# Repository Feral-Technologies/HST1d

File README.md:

HST1d FERAL TECHNOLOGIES AKA The Music Technology Frisbee (as christened by Electronic Instruments students 2018) is a six-voice portable and battery powered synthesiser based around a 40106 (Hex Schmitt-Trigger). 

Three voices are operated via resistive-touch on the MuTec lettering;

Three voices can be either light-sensitive (photocells) or controlled via potentiometers, the control method is individually switchable for each of these three voices;

The range of the three light/potentiometer-controlled voices is switchable high/low;

Lighting/pitch control is laid out horizontally across the board while from an output perspective the instrument is divided in half down the middle, with two separate volume controls: one for the three touch sensitive voices and the other for the three light/potentiometer voices;

The three individual voices that make up each of the two halves of the instrument can either be mixed via diodes or resistors (switchable), which offers further timbral manipulation;

Output is via mono ¼ inch jack socket on the rear (along with the off/on switch) and/or the onboard amplifier/speaker combination using an LM386 (switchable, and both can be used simultaneously, though there’s no buffering so this can impact tone–I should add an op-amp in future);

Power is via 9-volt battery which clips into a socket on the rear, this also makes the whole thing stable and sit nicely/angled towards the performer when used as as a desktop instrument;

LEDs articulate interactions with the touch-sensitive side of the circuit;

Two of the LEDs on the touch circuit are deliberately placed near the photocells that control two of the other voices, if desired these can be bent towards each other (and even taped together/mounted in a straw) for vactrol fun and interaction.

In case anyone actually try to build this it’s worth noting this I had to make my own footprints for the switches as I had bought a large quantity very cheaply and the spacing was not quite what I anticipated, some standard switches do not fit – always best to print out and check components by pushing through the paper! (I learned this the hard way…..)

See HST1d_Feral_Technologies_2018.pdf for full build documentation with step-by-step build instructions, parts list, and a photograph of each stage (this was made for my 2018 teaching of 2710QCM Electronic Instruments @ QCGU).

More information 
http://www.johnrobertferguson.com/hst1d-feral-technologies/

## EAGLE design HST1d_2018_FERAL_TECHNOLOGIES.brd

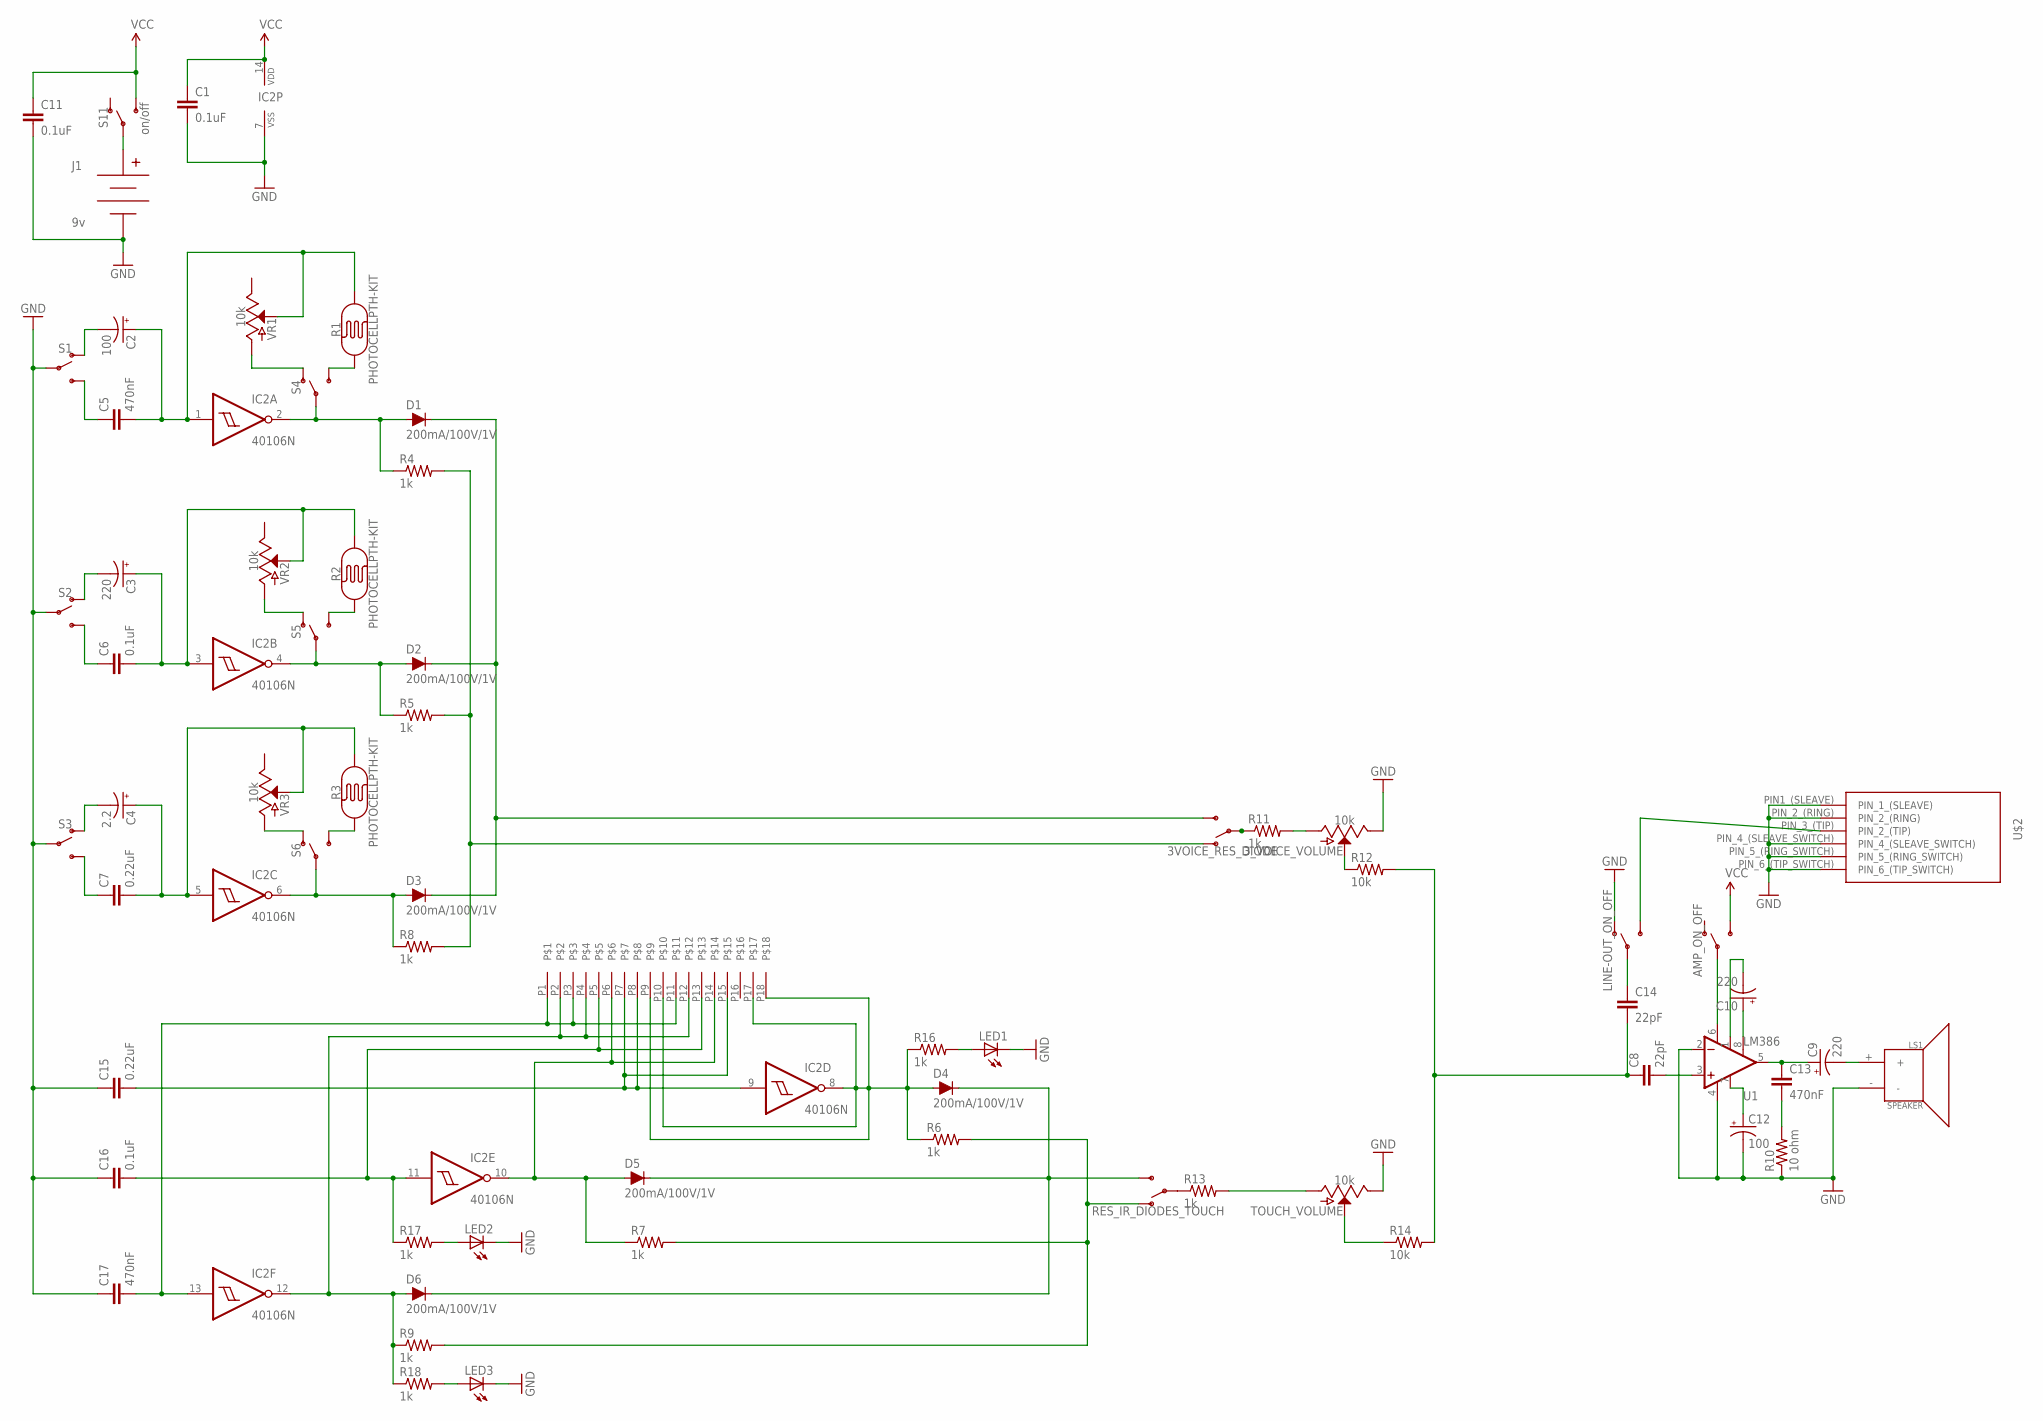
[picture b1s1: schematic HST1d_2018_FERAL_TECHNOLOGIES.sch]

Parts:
3VOICE_RES_DIODE: SWITCH-SPDT-PTH-11.6X4.0MM; SWITCH_SPDT_PTH_11.6X4.0MM
3_VOICE_VOLUME: 10k; POT-PTH-ALPS
AMP_ON_OFF: SWITCH-SPDT-PTH-11.6X4.0MM; SWITCH_SPDT_PTH_11.6X4.0MM
C1, C6, C11, C16: 0.1uF; CAP-PTH-SMALL-KIT
C2, C12: 100; CPOL-RADIAL-100UF-25V
C3, C9, C10: 220; CPOL-RADIAL-100UF-25V
C4: 2.2; CPOL-RADIAL-100UF-25V
C5, C17: 470nF; CAP-PTH-SMALL-KIT
C7, C15: 0.22uF; CAP-PTH-SMALL-KIT
C8, C14: 22pF; CAP-PTH-2.54
C13: 470nF; CAP-PTH-SMALLEZ
D1, D2, D3, D4, D5, D6: 200mA/100V/1V; DIODE-1N4148
IC2: 40106N; DIL14
J1: 9v; BC9VPC
LED1, LED2, LED3: LED5MM
LINE-OUT_ON_OFF: SWITCH-SPDT-PTH-11.6X4.0MM; SWITCH_SPDT_PTH_11.6X4.0MM
LS1: SPEAKER; PCB_MOUNT_SPEAKER
R1, R2, R3: PHOTOCELLPTH-KIT; PHOTOCELL-KIT
R4, R5, R6, R7, R8, R9, R11, R13, R16, R17, R18: 1k; AXIAL-0.4
R10: 10 ohm; AXIAL-0.4
R12, R14: 10k; AXIAL-0.4
RES_IR_DIODES_TOUCH: SWITCH-SPDT-PTH-11.6X4.0MM; SWITCH_SPDT_PTH_11.6X4.0MM
S1, S2, S3, S4, S5, S6: SWITCH-SPDT-PTH-11.6X4.0MM; SWITCH_SPDT_PTH_11.6X4.0MM
S11: on/off; SWITCH_SPDT_PTH_11.6X4.0MM
TOUCH_VOLUME: 10k; POT-PTH-ALPS
U1: LM386; DIP08
U$1: MT_TOUCH_POINT; TOUCH_POINT
U$2: 0.25_INCH_TRS_SWITCHED_AUDIO_SOCKET; 0.25INCH_AUDIO_SOCKET
VR1, VR2, VR3: 10k; POT-PTH-ALPS

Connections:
GND: 3_VOICE_VOLUME.P$1 (E), C1.2, C11.2, C12.2 (-), C15.1, C16.1, C17.1, IC2.7 (VSS), J1.V-, LED1.K (C), LED2.K (C), LED3.K (C), LINE-OUT_ON_OFF.1 (O), LS1.-, R10.P$1 (1), S1.2, S2.2, S3.2, TOUCH_VOLUME.P$1 (E), U1.2 (-IN), U1.4 (V-), U$2.PIN1_(SLEAVE) (PIN_1_(SLEAVE)), U$2.PIN_2_(RING), U$2.PIN_4_(SLEAVE_SWITC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, U$2.PIN_5_(RING_SWITCH), U$2.PIN_6_(TIP_SWITCH)
unnamed: C2.2 (-), S1.1 (O)
unnamed: C3.2 (-), S2.1 (O)
unnamed: C4.2 (-), S3.1 (O)
unnamed: C5.1, S1.3 (S)
unnamed: C2.1 (+), C5.2, IC2.1 (I), R1.2, VR1.P$2 (S)
unnamed: C6.1, S2.3 (S)
unnamed: D2.A, IC2.4 (O), R5.P$1 (1), S5.2
unnamed: C7.1, S3.3 (S)
unnamed: R1.1, S4.3 (S)
unnamed: D3.A, IC2.6 (O), R8.P$1 (1), S6.2
unnamed: S4.1 (O), VR1.P$3 (A)
unnamed: D1.A, IC2.2 (O), R4.P$1 (1), S4.2
unnamed: R6.P$2 (2), R7.P$2 (2), R9.P$2 (2), RES_IR_DIODES_TOUCH.1 (O)
unnamed: S5.1 (O), VR2.P$3 (A)
unnamed: R2.1, S5.3 (S)
unnamed: R3.1, S6.3 (S)
unnamed: C3.1 (+), C6.2, IC2.3 (I), R2.2, VR2.P$2 (S)
unnamed: C4.1 (+), C7.2, IC2.5 (I), R3.2, VR3.P$2 (S)
unnamed: 3_VOICE_VOLUME.P$2 (S), R12.P$1 (1)
unnamed: 3VOICE_RES_DIODE.3 (S), D1.C, D2.C, D3.C
unnamed: LINE-OUT_ON_OFF.3 (S), U$2.PIN_3_(TIP) (PIN_2_(TIP))
unnamed: R14.P$1 (1), TOUCH_VOLUME.P$2 (S)
unnamed: 3VOICE_RES_DIODE.1 (O), R4.P$2 (2), R5.P$2 (2), R8.P$2 (2)
unnamed: C15.2, IC2.9 (I), U$1.P7, U$1.P8, U$1.P15
unnamed: C14.1, LINE-OUT_ON_OFF.2
unnamed: LED2.A, R17.P$2 (2)
unnamed: C9.1 (+), C13.1, U1.5 (OUT)
unnamed: D4.A, IC2.8 (O), R6.P$1 (1), R16.P$1 (1), U$1.P9, U$1.P10, U$1.P17, U$1.P18
unnamed: J1.V+, S11.2
unnamed: D5.A, IC2.10 (O), R7.P$1 (1), U$1.P6, U$1.P14
unnamed: R13.P$2 (2), TOUCH_VOLUME.P$3 (A)
unnamed: C8.2, U1.3 (+IN)
unnamed: C9.2 (-), LS1.+
unnamed: C12.1 (+), U1.7 (BP)
unnamed: S6.1 (O), VR3.P$3 (A)
unnamed: C10.1 (+), U1.8 (GAIN)
unnamed: C10.2 (-), U1.1 (GAIN)
unnamed: C13.2, R10.P$2 (2)
unnamed: C8.1, C14.2, R12.P$2 (2), R14.P$2 (2)
unnamed: D6.A, IC2.12 (O), R9.P$1 (1), R18.P$1 (1), U$1.P2, U$1.P4, U$1.P12
unnamed: AMP_ON_OFF.2, U1.6 (V+)
unnamed: LED1.A, R16.P$2 (2)
unnamed: D4.C, D5.C, D6.C, RES_IR_DIODES_TOUCH.3 (S)
unnamed: C16.2, IC2.11 (I), R17.P$1 (1), U$1.P5, U$1.P13
unnamed: R13.P$1 (1), RES_IR_DIODES_TOUCH.2
unnamed: C17.2, IC2.13 (I), U$1.P1, U$1.P3, U$1.P11
unnamed: LED3.A, R18.P$2 (2)
unnamed: 3_VOICE_VOLUME.P$3 (A), R11.P$2 (2)
RES_OR_DIODES_3_VOICES: 3VOICE_RES_DIODE.2, R11.P$1 (1)
VCC: AMP_ON_OFF.3 (S), C1.1, C11.1, IC2.14 (VDD), S11.3 (S)

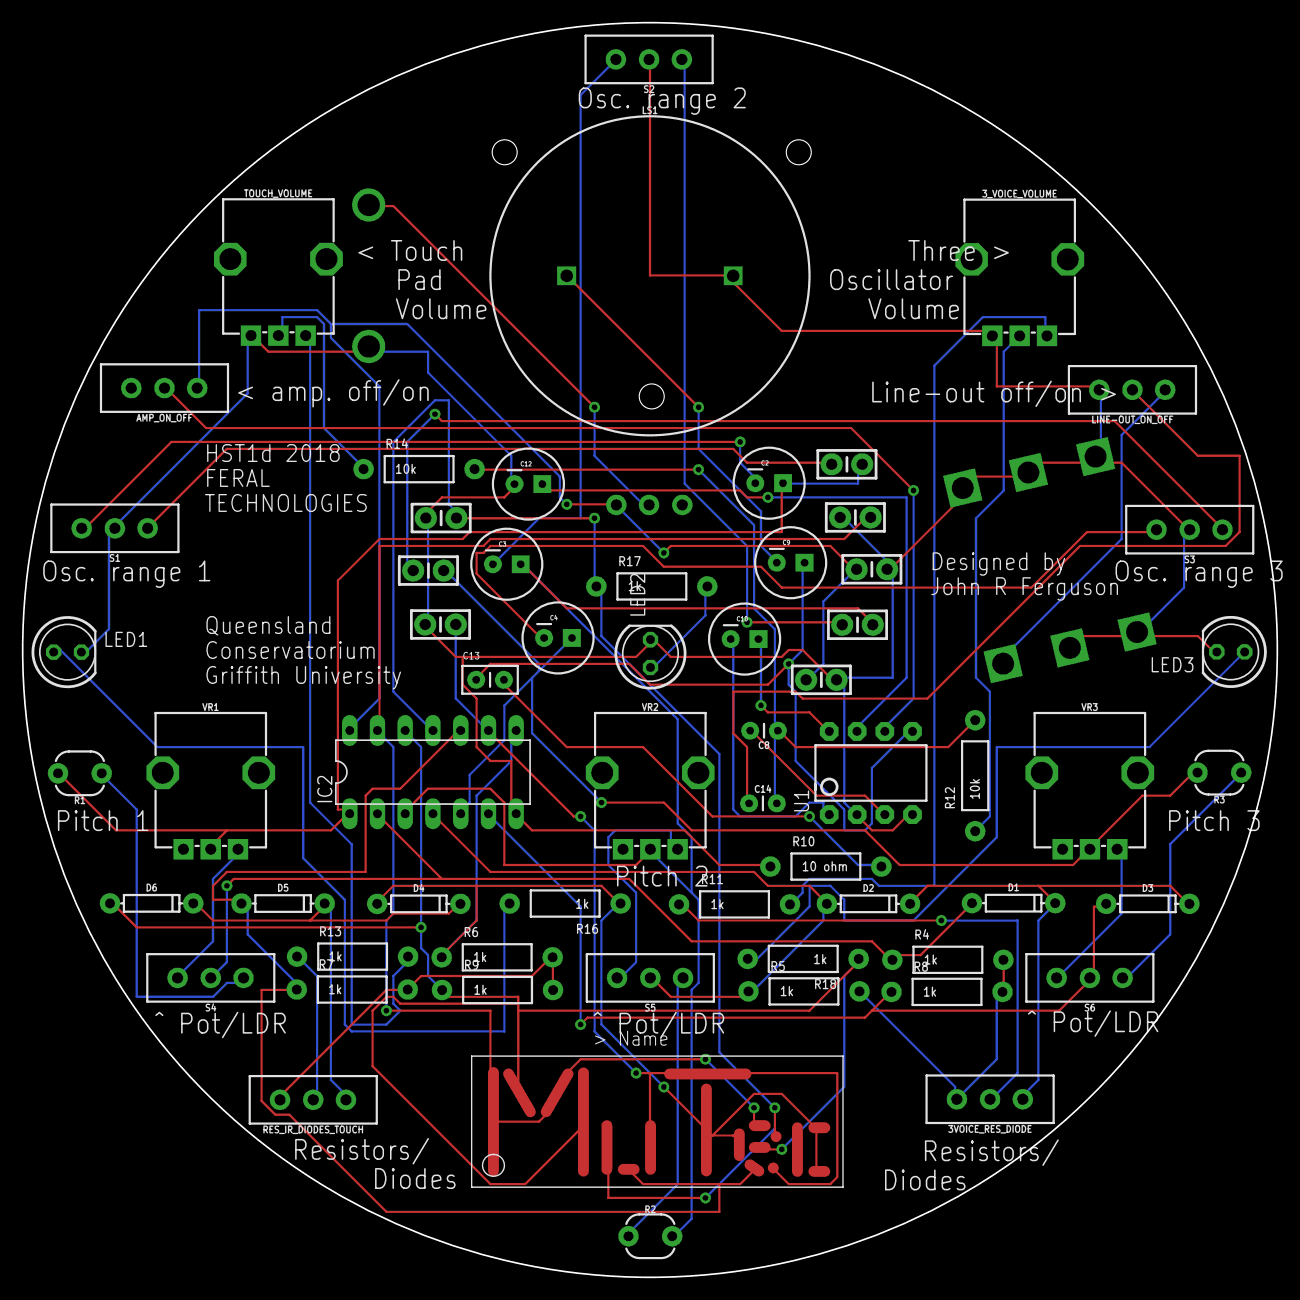
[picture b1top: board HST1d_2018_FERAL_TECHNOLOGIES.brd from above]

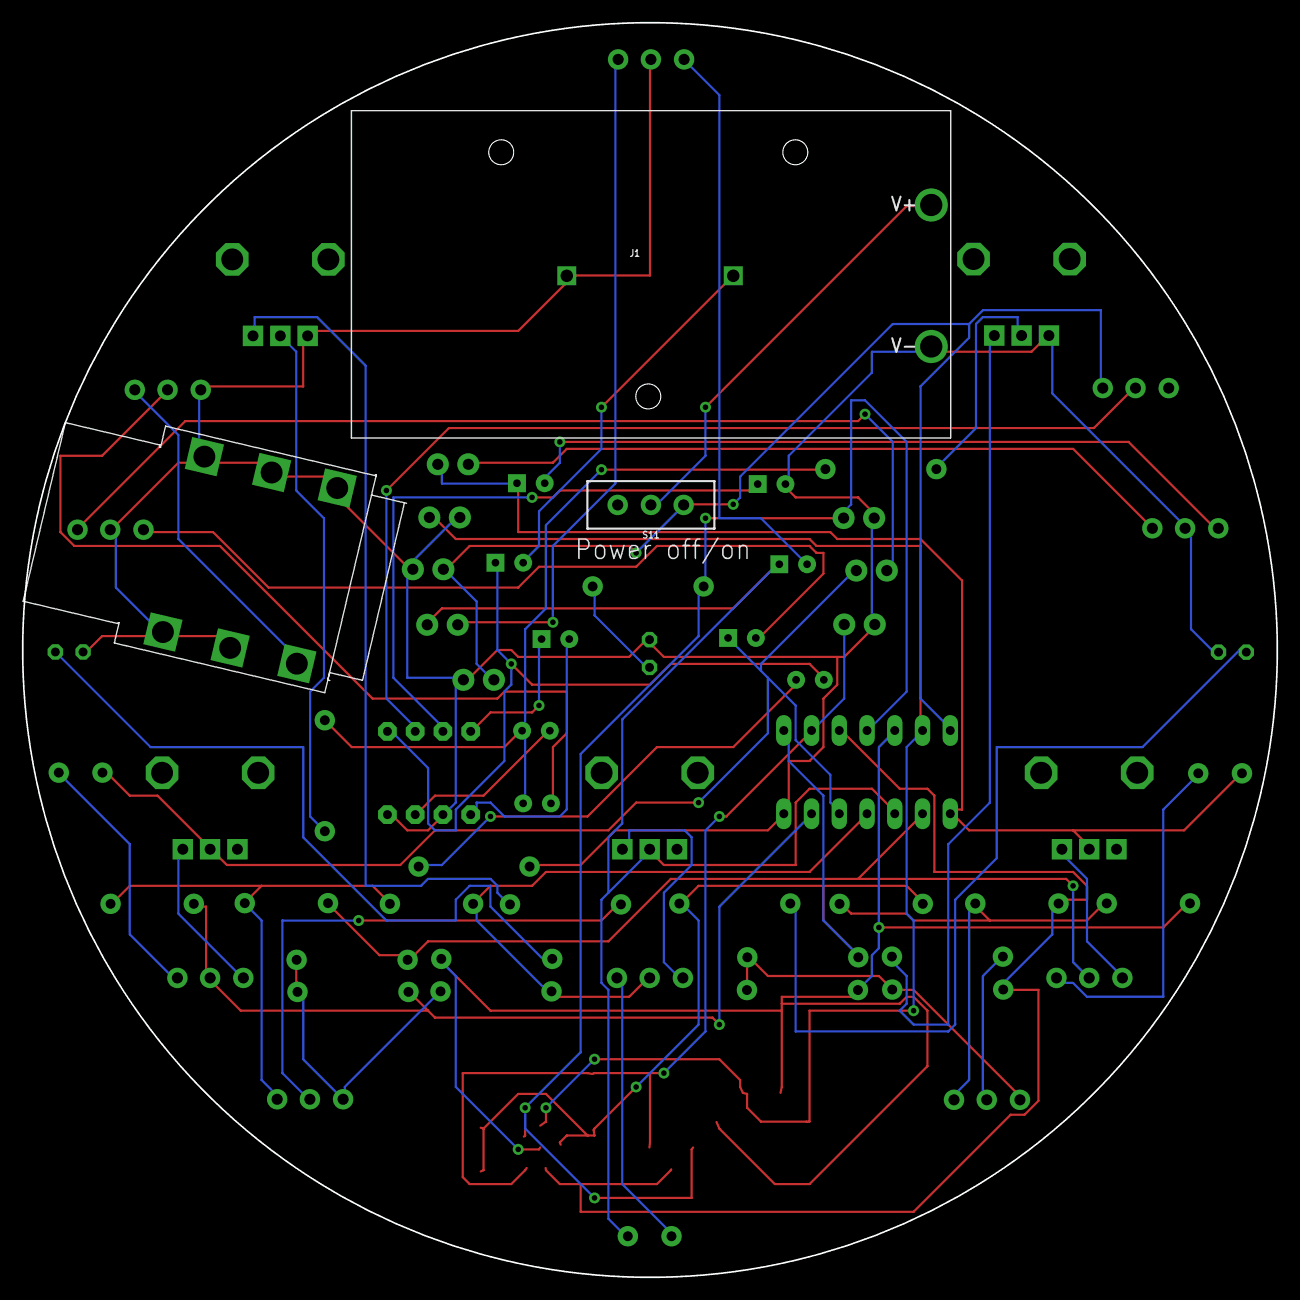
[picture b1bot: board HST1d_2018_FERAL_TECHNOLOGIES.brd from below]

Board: 2 copper layers, 114.9 x 114.9 mm, 65 parts (3 on the bottom side), 51 nets.

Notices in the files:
parts and their libraries:
SparkFun-Capacitors: Licensing: Creative Commons ShareAlike 4.0 International - https://creativecommons.org/licenses/by-sa/4.0
